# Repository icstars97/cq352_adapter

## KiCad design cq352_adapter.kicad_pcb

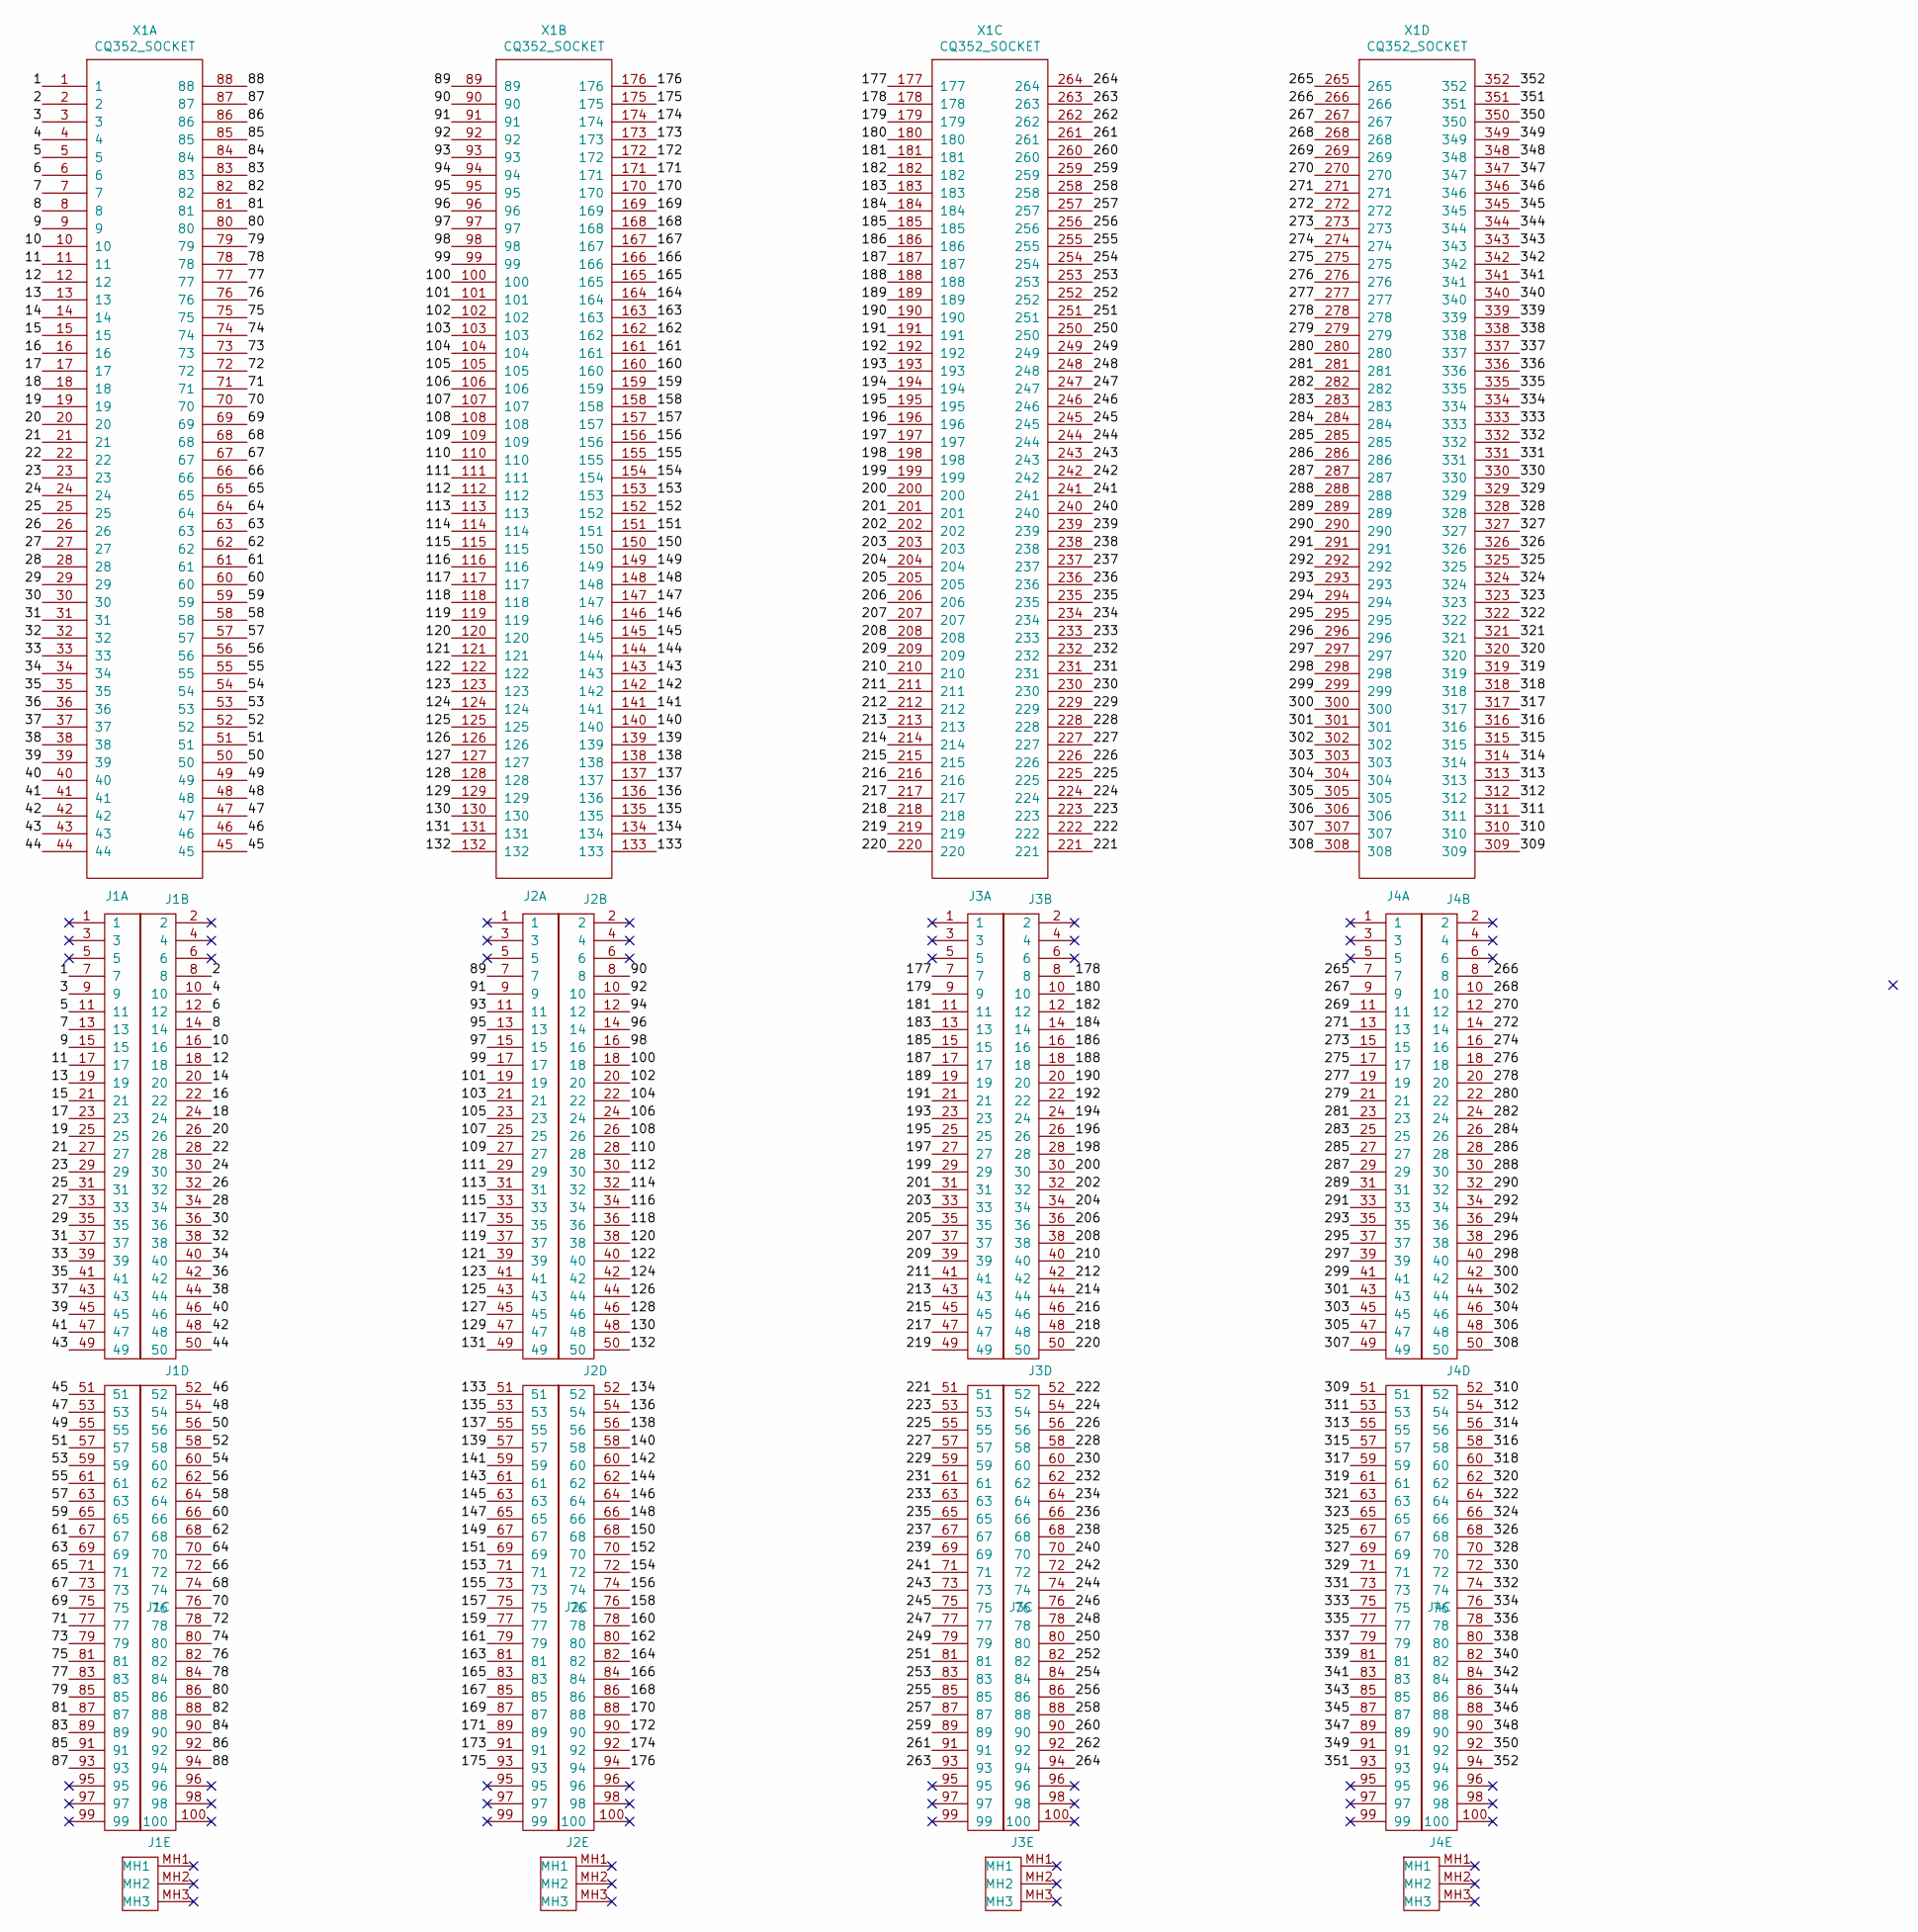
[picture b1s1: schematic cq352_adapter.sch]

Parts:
J1, J2, J3, J4: FSI-150; FSI-150-10-L-D-M-AD
X1: CQ352_SOCKET; cq352_socket

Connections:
/1: J1.7, X1.1
/2: J1.8, X1.2
/3: J1.9, X1.3
/4: J1.10, X1.4
/5: J1.11, X1.5
/6: J1.12, X1.6
/7: J1.13, X1.7
/8: J1.14, X1.8
/9: J1.15, X1.9
/10: J1.16, X1.10
/11: J1.17, X1.11
/12: J1.18, X1.12
/13: J1.19, X1.13
/14: J1.20, X1.14
/15: J1.21, X1.15
/16: J1.22, X1.16
/17: J1.23, X1.17
/18: J1.24, X1.18
/19: J1.25, X1.19
/20: J1.26, X1.20
/21: J1.27, X1.21
/22: J1.28, X1.22
/23: J1.29, X1.23
/24: J1.30, X1.24
/25: J1.31, X1.25
/26: J1.32, X1.26
/27: J1.33, X1.27
/28: J1.34, X1.28
/29: J1.35, X1.29
/30: J1.36, X1.30
/31: J1.37, X1.31
/32: J1.38, X1.32
/33: J1.39, X1.33
/34: J1.40, X1.34
/35: J1.41, X1.35
/36: J1.42, X1.36
/37: J1.43, X1.37
/38: J1.44, X1.38
/39: J1.45, X1.39
/40: J1.46, X1.40
/41: J1.47, X1.41
/42: J1.48, X1.42
/43: J1.49, X1.43
/44: J1.50, X1.44
/45: J1.51, X1.45
/46: J1.52, X1.46
/47: J1.53, X1.47
/48: J1.54, X1.48
/49: J1.55, X1.49
/50: J1.56, X1.50
/51: J1.57, X1.51
/52: J1.58, X1.52
/53: J1.59, X1.53
/54: J1.60, X1.54
/55: J1.61, X1.55
/56: J1.62, X1.56
/57: J1.63, X1.57
/58: J1.64, X1.58
/59: J1.65, X1.59
/60: J1.66, X1.60
/61: J1.67, X1.61
/62: J1.68, X1.62
/63: J1.69, X1.63
/64: J1.70, X1.64
/65: J1.71, X1.65
/66: J1.72, X1.66
/67: J1.73, X1.67
/68: J1.74, X1.68
/69: J1.75, X1.69
/70: J1.76, X1.70
/71: J1.77, X1.71
/72: J1.78, X1.72
/73: J1.79, X1.73
/74: J1.80, X1.74
/75: J1.81, X1.75
/76: J1.82, X1.76
/77: J1.83, X1.77
/78: J1.84, X1.78
/79: J1.85, X1.79
/80: J1.86, X1.80
/81: J1.87, X1.81
/82: J1.88, X1.82
/83: J1.89, X1.83
/84: J1.90, X1.84
/85: J1.91, X1.85
/86: J1.92, X1.86
/87: J1.93, X1.87
/88: J1.94, X1.88
/89: J2.7, X1.89
/90: J2.8, X1.90
/91: J2.9, X1.91
/92: J2.10, X1.92
/93: J2.11, X1.93
/94: J2.12, X1.94
/95: J2.13, X1.95
/96: J2.14, X1.96
/97: J2.15, X1.97
/98: J2.16, X1.98
/99: J2.17, X1.99
/100: J2.18, X1.100
/101: J2.19, X1.101
/102: J2.20, X1.102
/103: J2.21, X1.103
/104: J2.22, X1.104
/105: J2.23, X1.105
/106: J2.24, X1.106
/107: J2.25, X1.107
/108: J2.26, X1.108
/109: J2.27, X1.109
/110: J2.28, X1.110
/111: J2.29, X1.111
/112: J2.30, X1.112
/113: J2.31, X1.113
/114: J2.32, X1.114
/115: J2.33, X1.115
/116: J2.34, X1.116
/117: J2.35, X1.117
/118: J2.36, X1.118
/119: J2.37, X1.119
/120: J2.38, X1.120
/121: J2.39, X1.121
/122: J2.40, X1.122
/123: J2.41, X1.123
/124: J2.42, X1.124
/125: J2.43, X1.125
/126: J2.44, X1.126
/127: J2.45, X1.127
/128: J2.46, X1.128
/129: J2.47, X1.129
/130: J2.48, X1.130
/131: J2.49, X1.131
/132: J2.50, X1.132
/133: J2.51, X1.133
/134: J2.52, X1.134
/135: J2.53, X1.135
/136: J2.54, X1.136
/137: J2.55, X1.137
/138: J2.56, X1.138
/139: J2.57, X1.139
/140: J2.58, X1.140
/141: J2.59, X1.141
/142: J2.60, X1.142
/143: J2.61, X1.143
/144: J2.62, X1.144
/145: J2.63, X1.145
/146: J2.64, X1.146
/147: J2.65, X1.147
/148: J2.66, X1.148
/149: J2.67, X1.149
/150: J2.68, X1.150
/151: J2.69, X1.151
/152: J2.70, X1.152
/153: J2.71, X1.153
/154: J2.72, X1.154
/155: J2.73, X1.155
/156: J2.74, X1.156
/157: J2.75, X1.157
/158: J2.76, X1.158
/159: J2.77, X1.159
/160: J2.78, X1.160
/161: J2.79, X1.161
/162: J2.80, X1.162
/163: J2.81, X1.163
/164: J2.82, X1.164
/165: J2.83, X1.165
/166: J2.84, X1.166
/167: J2.85, X1.167
/168: J2.86, X1.168
/169: J2.87, X1.169
/170: J2.88, X1.170
/171: J2.89, X1.171
/172: J2.90, X1.172
/173: J2.91, X1.173
/174: J2.92, X1.174
/175: J2.93, X1.175
/176: J2.94, X1.176
/177: J3.7, X1.177
/178: J3.8, X1.178
/179: J3.9, X1.179
/180: J3.10, X1.180
/181: J3.11, X1.181
/182: J3.12, X1.182
/183: J3.13, X1.183
/184: J3.14, X1.184
/185: J3.15, X1.185
/186: J3.16, X1.186
/187: J3.17, X1.187
/188: J3.18, X1.188
/189: J3.19, X1.189
/190: J3.20, X1.190
/191: J3.21, X1.191
/192: J3.22, X1.192
/193: J3.23, X1.193
/194: J3.24, X1.194
/195: J3.25, X1.195
/196: J3.26, X1.196
/197: J3.27, X1.197
/198: J3.28, X1.198
/199: J3.29, X1.199
/200: J3.30, X1.200
/201: J3.31, X1.201
/202: J3.32, X1.202
/203: J3.33, X1.203
/204: J3.34, X1.204
/205: J3.35, X1.205
/206: J3.36, X1.206
/207: J3.37, X1.207
/208: J3.38, X1.208
/209: J3.39, X1.209
/210: J3.40, X1.210
/211: J3.41, X1.211
/212: J3.42, X1.212
/213: J3.43, X1.213
/214: J3.44, X1.214
/215: J3.45, X1.215
/216: J3.46, X1.216
/217: J3.47, X1.217
/218: J3.48, X1.218
/219: J3.49, X1.219
/220: J3.50, X1.220
/221: J3.51, X1.221
/222: J3.52, X1.222
/223: J3.53, X1.223
/224: J3.54, X1.224
/225: J3.55, X1.225
/226: J3.56, X1.226
/227: J3.57, X1.227
/228: J3.58, X1.228
/229: J3.59, X1.229
/230: J3.60, X1.230
/231: J3.61, X1.231
/232: J3.62, X1.232
/233: J3.63, X1.233
/234: J3.64, X1.234
/235: J3.65, X1.235
/236: J3.66, X1.236
/237: J3.67, X1.237
/238: J3.68, X1.238
/239: J3.69, X1.239
/240: J3.70, X1.240
/241: J3.71, X1.241
/242: J3.72, X1.242
/243: J3.73, X1.243
/244: J3.74, X1.244
/245: J3.75, X1.245
/246: J3.76, X1.246
/247: J3.77, X1.247
/248: J3.78, X1.248
/249: J3.79, X1.249
/250: J3.80, X1.250
/251: J3.81, X1.251
/252: J3.82, X1.252
/253: J3.83, X1.253
/254: J3.84, X1.254
/255: J3.85, X1.255
/256: J3.86, X1.256
/257: J3.87, X1.257
/258: J3.88, X1.258
/259: J3.89, X1.259
/260: J3.90, X1.260
/261: J3.91, X1.261
/262: J3.92, X1.262
/263: J3.93, X1.263
/264: J3.94, X1.264
/265: J4.7, X1.265
/266: J4.8, X1.266
/267: J4.9, X1.267
/268: J4.10, X1.268
/269: J4.11, X1.269
/270: J4.12, X1.270
/271: J4.13, X1.271
/272: J4.14, X1.272
/273: J4.15, X1.273
/274: J4.16, X1.274
/275: J4.17, X1.275
/276: J4.18, X1.276
/277: J4.19, X1.277
/278: J4.20, X1.278
/279: J4.21, X1.279
/280: J4.22, X1.280
/281: J4.23, X1.281
/282: J4.24, X1.282
/283: J4.25, X1.283
/284: J4.26, X1.284
/285: J4.27, X1.285
/286: J4.28, X1.286
/287: J4.29, X1.287
/288: J4.30, X1.288
/289: J4.31, X1.289
/290: J4.32, X1.290
/291: J4.33, X1.291
/292: J4.34, X1.292
/293: J4.35, X1.293
/294: J4.36, X1.294
/295: J4.37, X1.295
/296: J4.38, X1.296
/297: J4.39, X1.297
/298: J4.40, X1.298
/299: J4.41, X1.299
/300: J4.42, X1.300
/301: J4.43, X1.301
/302: J4.44, X1.302
/303: J4.45, X1.303
/304: J4.46, X1.304
/305: J4.47, X1.305
/306: J4.48, X1.306
/307: J4.49, X1.307
/308: J4.50, X1.308
/309: J4.51, X1.309
/310: J4.52, X1.310
/311: J4.53, X1.311
/312: J4.54, X1.312
/313: J4.55, X1.313
/314: J4.56, X1.314
/315: J4.57, X1.315
/316: J4.58, X1.316
/317: J4.59, X1.317
/318: J4.60, X1.318
/319: J4.61, X1.319
/320: J4.62, X1.320
/321: J4.63, X1.321
/322: J4.64, X1.322
/323: J4.65, X1.323
/324: J4.66, X1.324
/325: J4.67, X1.325
/326: J4.68, X1.326
/327: J4.69, X1.327
/328: J4.70, X1.328
/329: J4.71, X1.329
/330: J4.72, X1.330
/331: J4.73, X1.331
/332: J4.74, X1.332
/333: J4.75, X1.333
/334: J4.76, X1.334
/335: J4.77, X1.335
/336: J4.78, X1.336
/337: J4.79, X1.337
/338: J4.80, X1.338
/339: J4.81, X1.339
/340: J4.82, X1.340
/341: J4.83, X1.341
/342: J4.84, X1.342
/343: J4.85, X1.343
/344: J4.86, X1.344
/345: J4.87, X1.345
/346: J4.88, X1.346
/347: J4.89, X1.347
/348: J4.90, X1.348
/349: J4.91, X1.349
/350: J4.92, X1.350
/351: J4.93, X1.351
/352: J4.94, X1.352

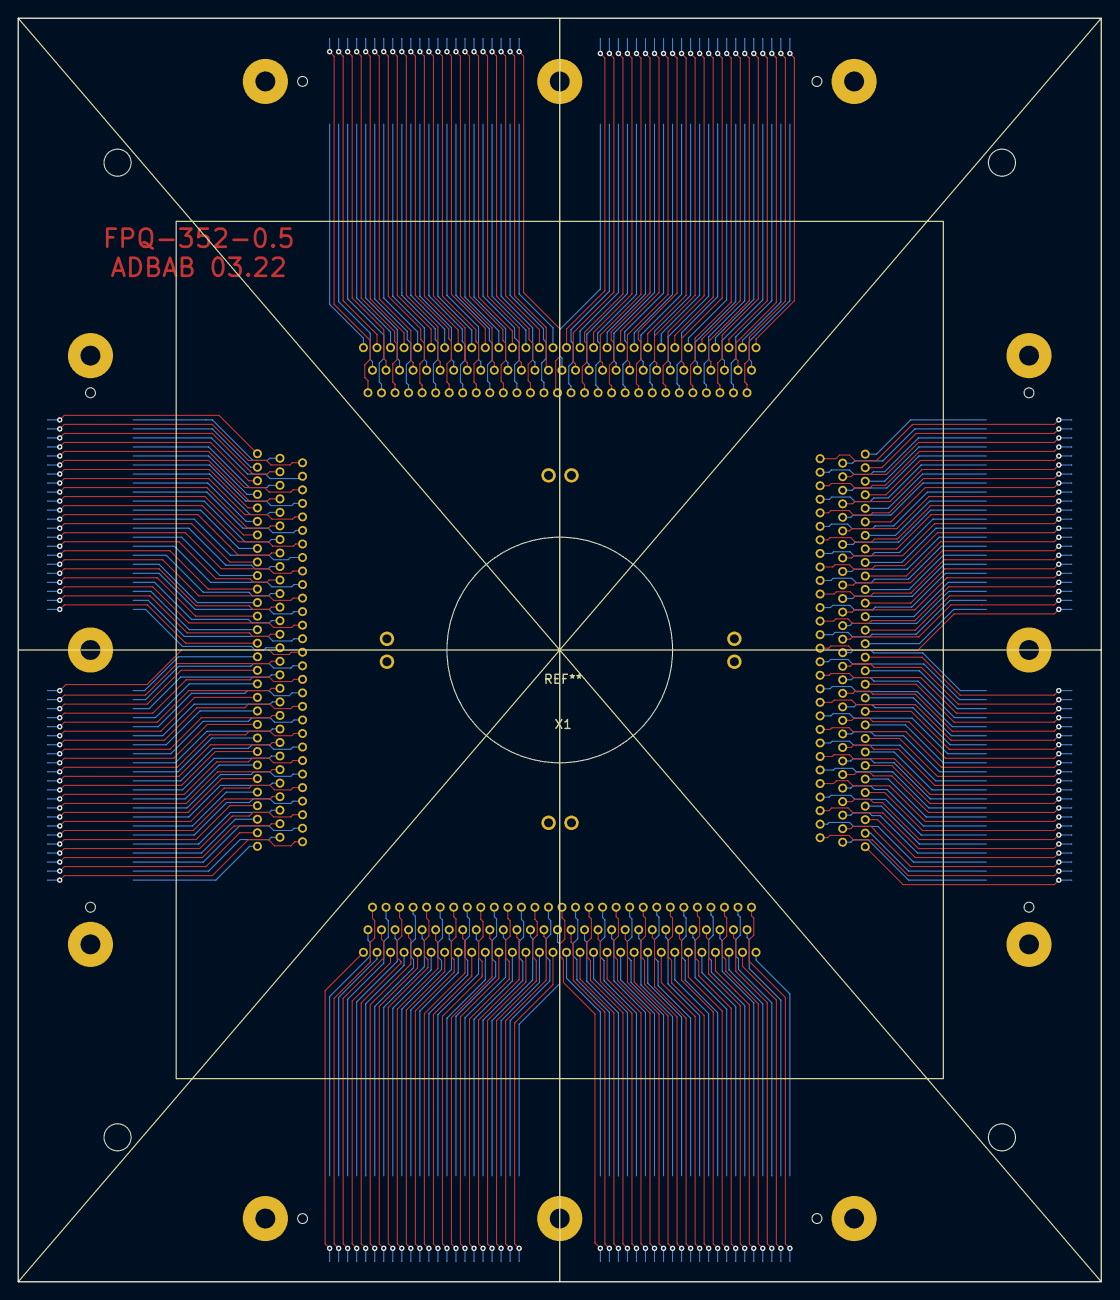
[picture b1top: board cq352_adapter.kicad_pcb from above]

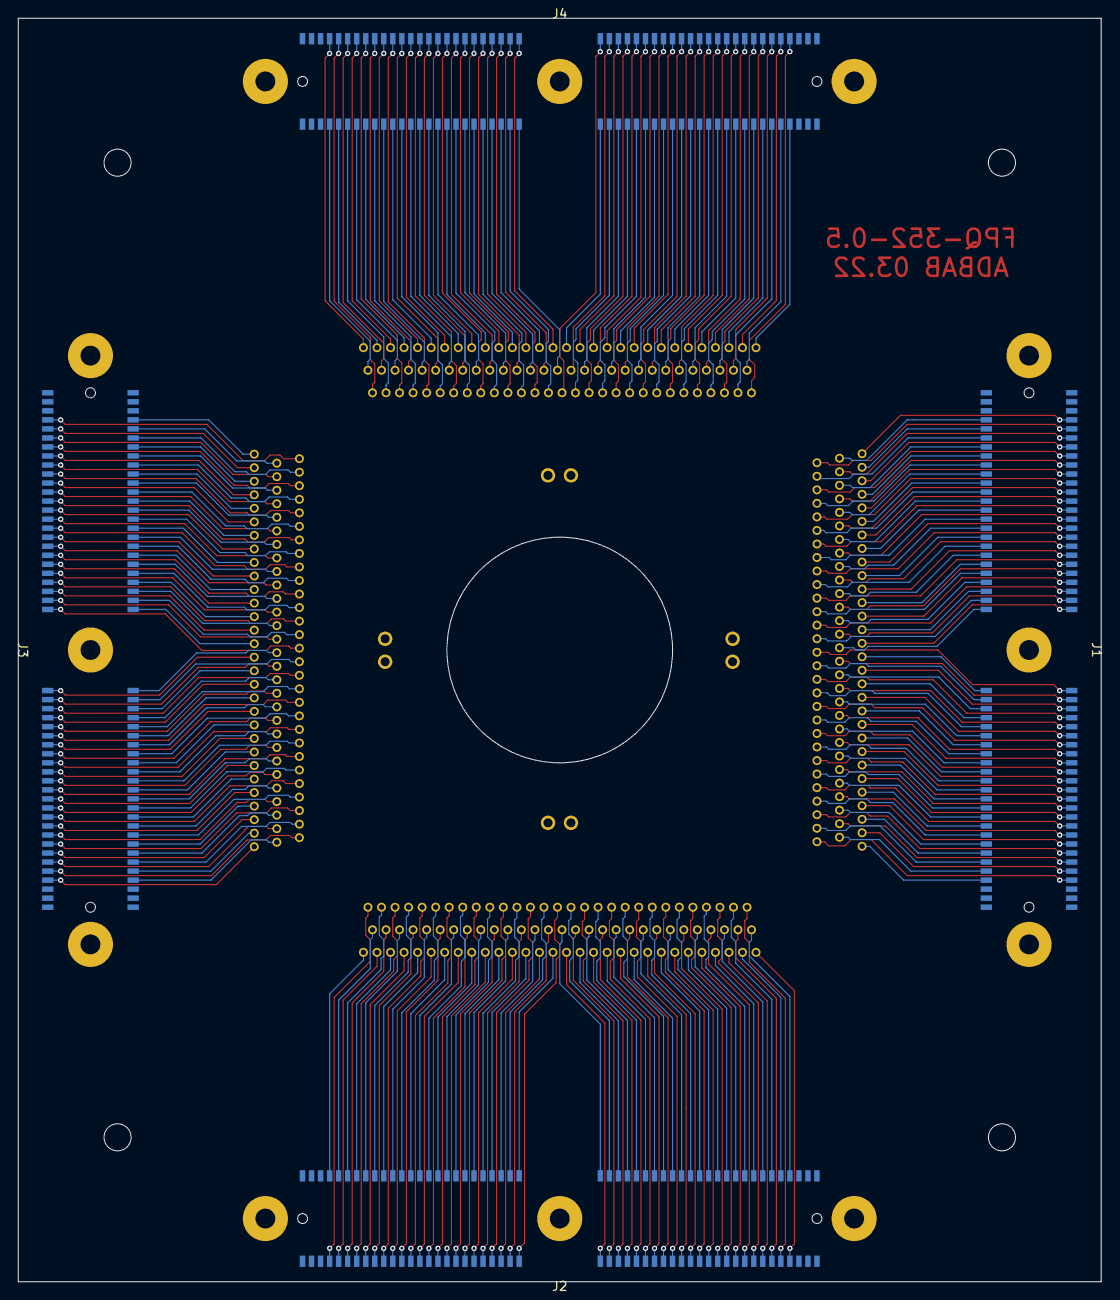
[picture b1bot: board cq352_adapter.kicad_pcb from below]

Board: 2 copper layers, 120.0 x 140.0 mm, 5 parts (4 on the bottom side), 352 nets.

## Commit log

2022-03-21 connector layout
2022-03-22 routing signals
2022-03-22 one side left to route
2022-03-23 finished routing
